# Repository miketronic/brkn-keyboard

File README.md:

# BR/KN
BR/KN Keyboard (Broken)

[More pictures here](images/)

## Features

- 28 keys (plus 2 small tactiles, bonus!)
- 2x 16mm trackballs - PMW3360 sensors
- USB connection between halves (or TRRS option as backup)
- Low profile choc switches with CFX spacing (closer spacing then standard choc, only caps of size 16.50mm x 16.50mm will fit)
- RGB lighting
- Waveshare RP2040 Zero controllers
- QMK firmware

## Introduction

The Broken (stylized BR/KN) keyboard is named because... 

  1. it's a split (a broken unibody)
  2. Broken by Seether was my wife and mine's wedding song that I wanted to honor and the day (queue awww's).  Ok enough on that, let's dig in.

I've always preferred small keebs and low switch counts.  The idea for this keyboard was to design a small split that also incorporated two trackballs (can use one for pointing, one for scrolling!), and have some other goodies like LEDs and tact switches for occasional needs like macros or toggling the RGB.

## Keymap

The layout is a larger rendition of my MM20 (3 column) layout with the addition of side columms.  I have no issues with my 20 key layout but it's a BIG change for users and having some keys like tab and backspace on dedicated keys can be convenient.  Of course with custom firmware you are not locked into any specific layout.  If you only want to combo 2 letters (24 non-thumb keys, 26 letters!), then that's totally fine.

The layout, MM28, leverages combos (the yellow letters shown below) for less-used letters, or where they "feel best".  I performed some studies on letter frequency in the English language and most common bigrams and trigrams to determine the letter placement. It kind of started off as Colemak from what I recall, maybe it's actually really different, I forgets.  P and B are weird, they both just barely made it to combos instead of their own letters even though I use them more often then I anticipated.  They could have gone somewhere like the U and W keys but with the frequency I use them I wanted them on my index and middle finger instead of putting all that work on my ring finger.

The biggest thing with starting a layout like this is to accept the fact that you'll start off at like 5wpm but your brain will take over and it'll become second nature eventually just like any other layout.  It's super fun and not making any lateral finger movements feels nice. 

## Keycaps

As noted in the *Features*, I chose a narrower keyswitch spacing and thus they require narrower keycaps.  CFX keycaps are commercially available from Chosfox, or you can print your own, for which I've included files in the keycaps folder.  They easily print upside down on an FDM printer, and I use a textured baseplate.

## Miscellaneous Notes

- For the switchplate, I put the plate on then soldered the switches.  Make sure you like your choice of filament that you printed the plate with because you're stuck with it ;).
- If you PCBA the board and the USB failed during manufacture, you can solder on a TRRS connector.  I have it designed to mount the TRRS on the bottom of the board to hide the connector and end of the cable within the case.  Also, you'll need to bodge two wires on the board to use TRRS, let me know if you need help if you go this route.
- The trackballs I used are 16mm polished mineral spheres I found on AliExpress.  I picked up a few different types of mineral and some were too large due to making a rock into a sphere not an exact science, so be mindful of that.  Alternatively, you can use human-made materials for a perfect spec 16mm ball.
- PCBA would be cheaper if you combine both halves with some mouse bites between them, feel free to do so or modify as you wish.  I did this version as a POC so it was cheaper if I messed up with one board than with both at the same time.

## The predecessor (CAP 5)

[Another shot](images/20240416_134642.jpg)

Contact with comments, questions, or if you build it!
- m1ketronic @discord
- mxb540@gmail.com

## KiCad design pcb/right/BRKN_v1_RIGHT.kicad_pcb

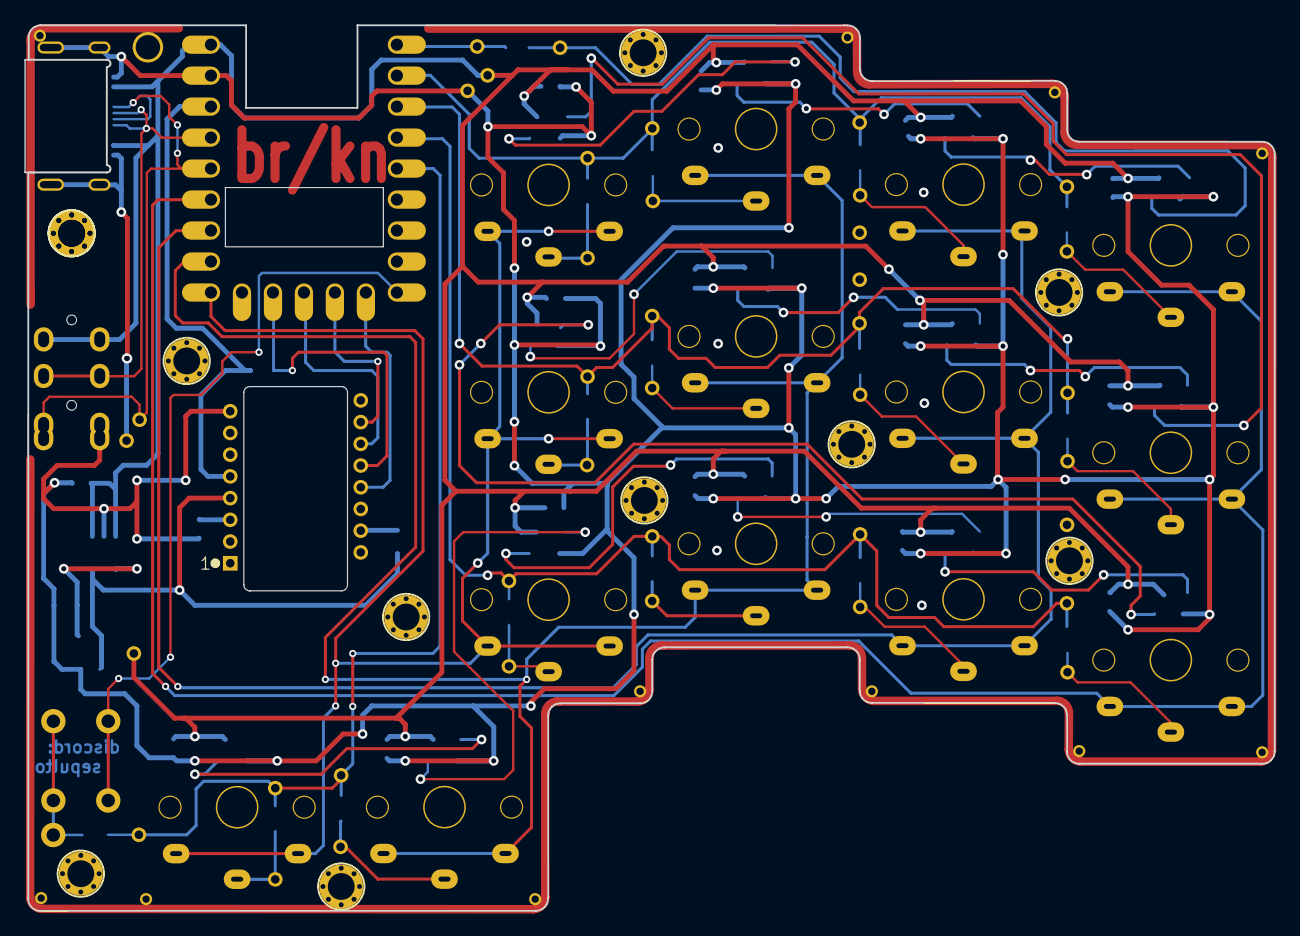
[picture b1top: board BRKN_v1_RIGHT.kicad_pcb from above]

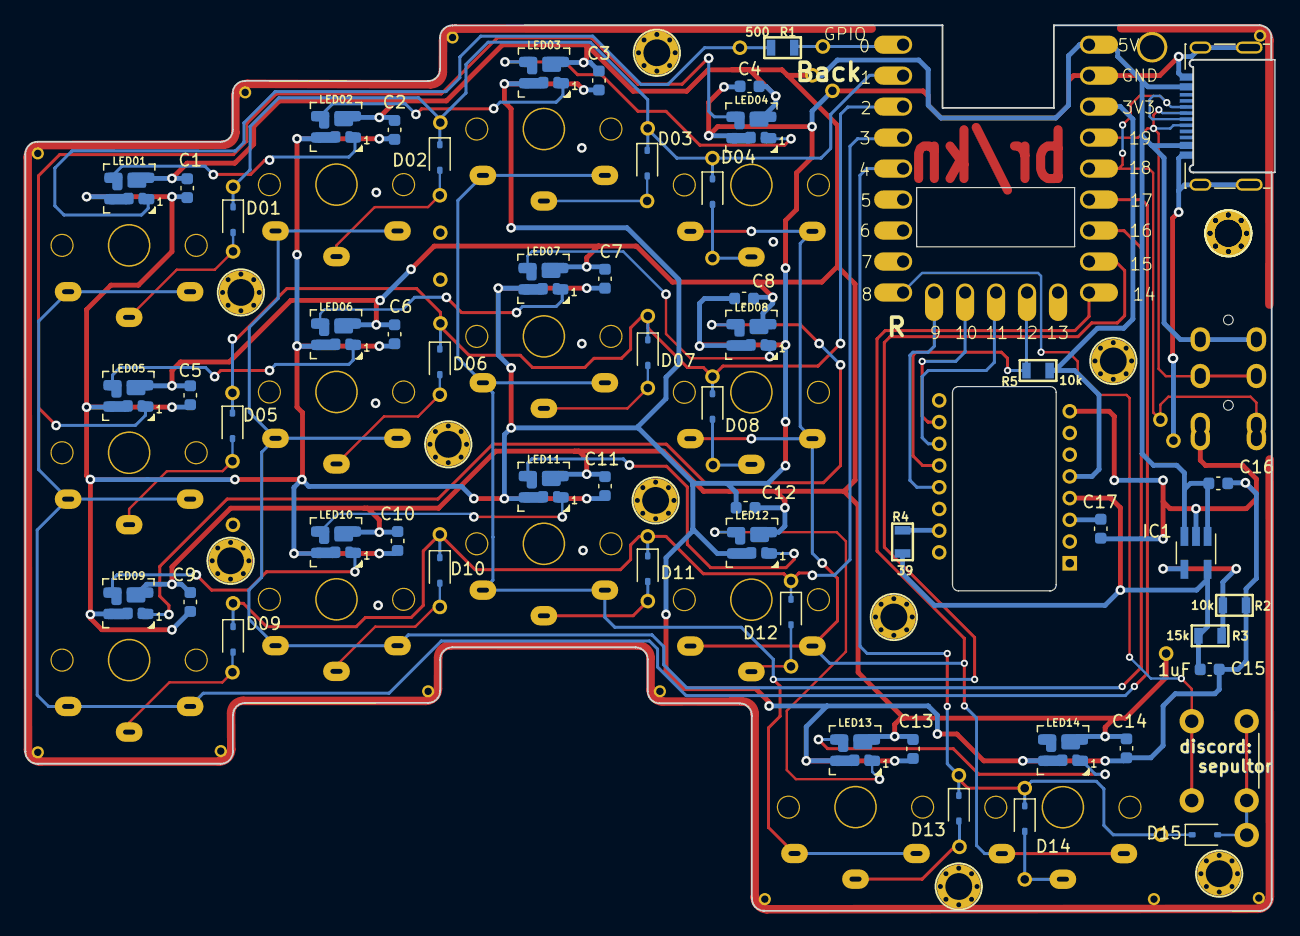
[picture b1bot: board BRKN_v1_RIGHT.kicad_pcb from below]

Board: 2 copper layers, 102.2 x 72.6 mm, 71 parts (69 on the bottom side), 52 nets.

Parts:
C1, C2, C3, C4, C5, C6, C7, C8, C9, C10, C11, C12, C13, C14, C15, C16: 1uF; C_0603_1608Metric
C17: 4.7uF; C_0603_1608Metric
D01, D02, D03, D04, D05, D06, D07, D08, D09, D10, D11, D12, D13, D14, D15: D; D_SOD-323
IC1: AP7335-WG-7; SOT-23-5_HandSoldering
J1: USB_C; MB_Molex-216990_USB_TYPE-C
LED01, LED02, LED03, LED04, LED05, LED06, LED07, LED08, LED09, LED10, LED11, LED12, LED13, LED14: SK6812MINI; MB_SK6812_Mini
R1: 500; R_0805
R2, R5: 10k; R_0805
R3: 15k; R_0805
R4: 39; R_0805
SW01, SW02, SW03, SW04, SW05, SW06, SW07, SW08, SW09, SW10, SW11, SW12, SW13, SW14: SW; MB_KailhChoc-1U_rev_17mm_oval
SW15: SW; MB_6x6_SW
U1: rp2040-zero; MB_rp2040-zero-001
U2: TRRS; MB_TRRS-PJ-320A
U3: PMW3360DM-T2QU; MB_PMW3360

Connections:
2V: C15.1, IC1.5 (OUT), R3.2, R4.1, U3.4 (VDD)
3V3: R5.1, U1.21 (3V3), U3.5 (VDDIO)
5V: C1.2, C2.2, C3.2, C4.2, C5.2, C6.2, C7.2, C8.2, C9.2, C10.2, C11.2, C12.2, C13.2, C14.2, C16.1, IC1.1 (IN), IC1.3 (EN), J1.A4 (VBUS), J1.A9 (VBUS), J1.B4 (VBUS), J1.B9 (VBUS), LED01.2 (VDD), LED02.2 (VDD), LED03.2 (VDD), LED04.2 (VDD), LED05.2 (VDD), LED06.2 (VDD), LED07.2 (VDD), LED08.2 (VDD), LED09.2 (VDD), LED10.2 (VDD), LED11.2 (VDD), LED12.2 (VDD), LED13.2 (VDD), LED14.2 (VDD), U1.23 (5V), U2.4 (RING2)
COL0: SW01.2, SW05.2, SW09.2, U1.18 (27)
COL1: SW02.2, SW06.2, SW10.2, U1.17 (26)
COL2: SW03.2, SW07.2, SW11.2, SW13.2, U1.16 (15)
COL3: SW04.2, SW08.2, SW12.2, SW14.2, U1.15 (14)
COL4: SW15.2, U1.9 (8)
GND: C1.1, C2.1, C3.1, C4.1, C5.1, C6.1, C7.1, C8.1, C9.1, C10.1, C11.1, C12.1, C13.1, C14.1, C15.2, C16.2, C17.2, IC1.2 (GND), J1.A1 (GND), J1.A12 (GND), J1.B1 (GND), J1.B12 (GND), J1.S1 (SHIELD), LED01.4 (VSS), LED02.4 (VSS), LED03.4 (VSS), LED04.4 (VSS), LED05.4 (VSS), LED06.4 (VSS), LED07.4 (VSS), LED08.4 (VSS), LED09.4 (VSS), LED10.4 (VSS), LED11.4 (VSS), LED12.4 (VSS), LED13.4 (VSS), LED14.4 (VSS), R2.2, U1.22 (GND), U2.1 (SLEEVE), U3.8 (GND)
LED: R1.1, U1.1 (0)
MISO: R5.2, U1.13 (12), U3.12 (MISO)
MOSI: U1.12 (11), U3.11 (MOSI)
NCS: U1.10 (9), U3.13 (NCS)
unnamed: D01.2, SW01.1
unnamed: D02.2, SW02.1
unnamed: D03.2, SW03.1
unnamed: D04.2, SW04.1
unnamed: D05.2, SW05.1
unnamed: D06.2, SW06.1
unnamed: D07.2, SW07.1
unnamed: D08.2, SW08.1
unnamed: D09.2, SW09.1
unnamed: D10.2, SW10.1
unnamed: D11.2, SW11.1
unnamed: D12.2, SW12.1
unnamed: D13.2, SW13.1
unnamed: D14.2, SW14.1
unnamed: D15.2, SW15.1
unnamed: IC1.4 (ADJ), R2.1, R3.1
unnamed: LED01.1 (DIN), R1.2
unnamed: LED01.3 (DOUT), LED02.1 (DIN)
unnamed: LED02.3 (DOUT), LED03.1 (DIN)
unnamed: LED03.3 (DOUT), LED04.1 (DIN)
unnamed: LED04.3 (DOUT), LED05.1 (DIN)
unnamed: LED05.3 (DOUT), LED06.1 (DIN)
unnamed: LED06.3 (DOUT), LED07.1 (DIN)
unnamed: LED07.3 (DOUT), LED08.1 (DIN)
unnamed: LED08.3 (DOUT), LED09.1 (DIN)
unnamed: LED09.3 (DOUT), LED10.1 (DIN)
unnamed: LED10.3 (DOUT), LED11.1 (DIN)
unnamed: LED11.3 (DOUT), LED12.1 (DIN)
unnamed: LED12.3 (DOUT), LED13.1 (DIN)
unnamed: LED13.3 (DOUT), LED14.1 (DIN)
unnamed: R4.2, U3.15 (LED_P)
unnamed: C17.1, U3.3 (VDDPIX)
ROW0: D01.1, D02.1, D03.1, D04.1, U1.2 (1)
ROW1: D05.1, D06.1, D07.1, D08.1, U1.3 (2)
ROW2: D09.1, D10.1, D11.1, D12.1, U1.4 (3)
ROW3: D13.1, D14.1, D15.1, U1.5 (4)
RX: J1.A7 (D-), J1.B7 (D-), U1.20 (29), U2.3 (RING1)
SCK: U1.11 (10), U3.10 (SCLK)
TX: J1.A6 (D+), J1.B6 (D+), U1.19 (28), U2.2 (TIP)

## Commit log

2024-04-15 Start of README.md
2024-04-15 Rename TTA_6_round_choc_short_fdm.stl to xMKBR_round_choc_short_fdm.stl
2024-04-16 QMK firmware files
2024-04-16 Upload images
2024-12-23 Create nofile
2024-12-23 Create x

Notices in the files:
README.md:
License: CC BY-SA 4.0
